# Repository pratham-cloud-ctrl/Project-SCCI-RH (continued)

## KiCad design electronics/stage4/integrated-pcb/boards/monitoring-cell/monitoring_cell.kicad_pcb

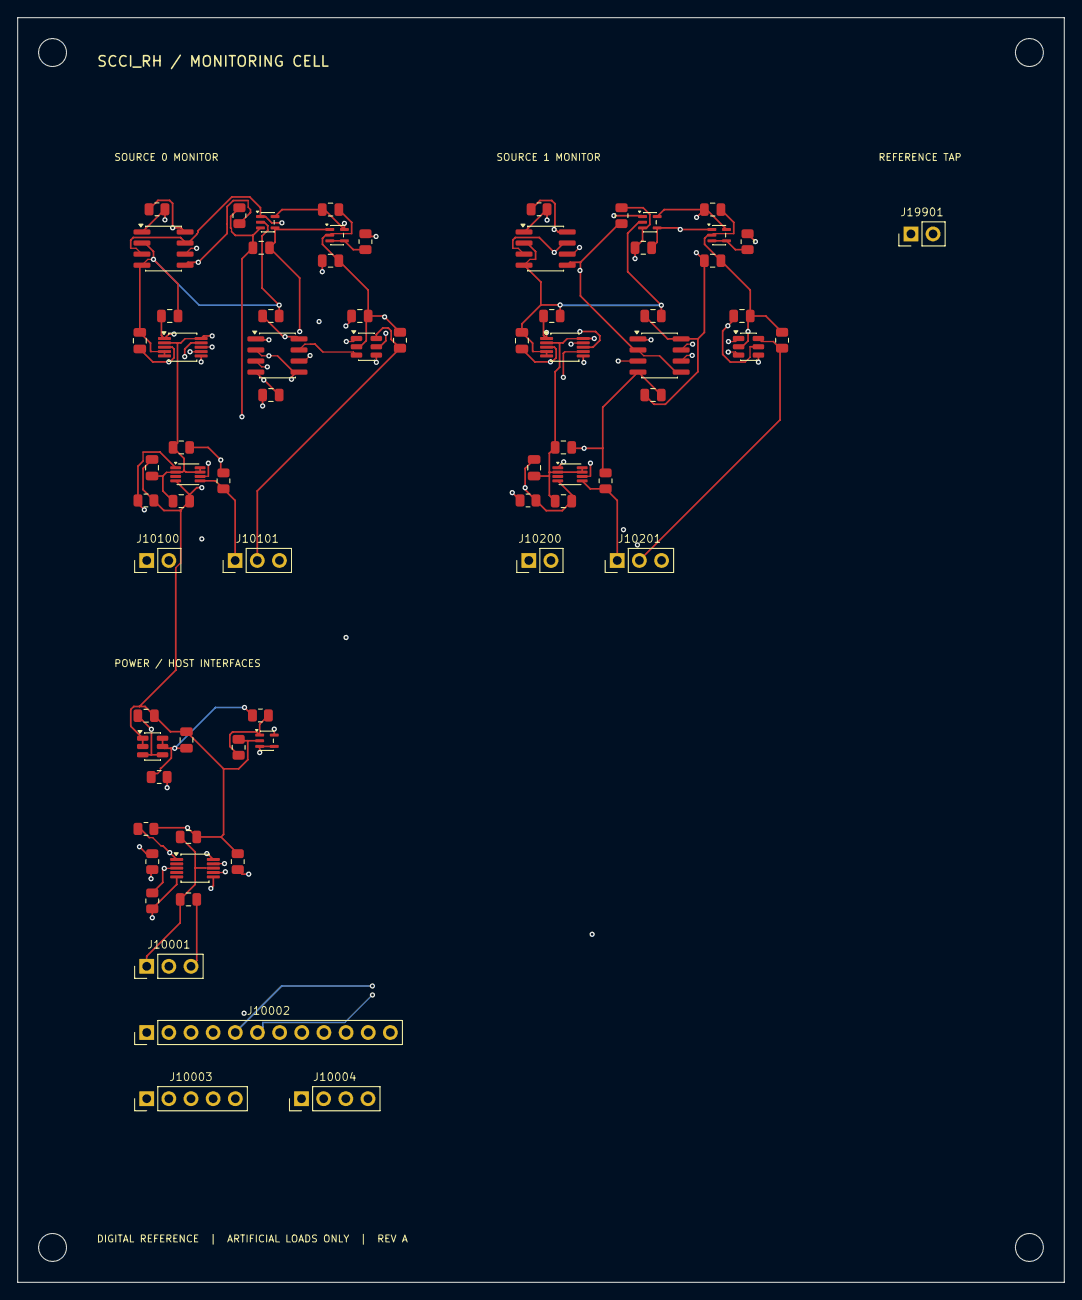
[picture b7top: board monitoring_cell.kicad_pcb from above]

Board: 4 copper layers, 120.0 x 145.0 mm, 75 parts (0 on the bottom side), 42 nets.

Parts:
C10001, C10002, C10105, C10106, C10205, C10206: 1u 10V; C_0805_2012Metric
C10003, C10004, C10102, C10103, C10104, C10108, C10109, C10110, C10202, C10203, C10204, C10208, C10209, C10210: 100n 10V; C_0805_2012Metric
C10100, C10200: 22n 0.5% C0G; C_0805_2012Metric
C10101, C10201: 1n C0G; C_0805_2012Metric
C10107, C10207: 22u 10V; C_0805_2012Metric
H1, H2, H3, H4: MountingHole_3.2mm_M3
J10001: LAB RAILS ONLY; PinHeader_1x03_P2.54mm_Vertical
J10002: MCU ENDPOINT/CONTROL; PinHeader_1x12_P2.54mm_Vertical
J10003: EXTERNAL SUPERVISION; PinHeader_1x05_P2.54mm_Vertical
J10004: CURRENT ADC INTERFACE; PinHeader_1x04_P2.54mm_Vertical
J10100: SOURCE 0 RETURN SHUNT; PinHeader_1x02_P2.54mm_Vertical
J10101: SOURCE 0 DRIVER PERMISSION; PinHeader_1x03_P2.54mm_Vertical
J10200: SOURCE 1 RETURN SHUNT; PinHeader_1x02_P2.54mm_Vertical
J10201: SOURCE 1 DRIVER PERMISSION; PinHeader_1x03_P2.54mm_Vertical
J19901: HOST TAP HARNESS; PinHeader_1x02_P2.54mm_Vertical
R10001, R10002, R10003, R10005, R10101, R10201: 10k 0.1%; R_0805_2012Metric
R10004: 19.1k 0.1%; R_0805_2012Metric
R10006, R10007, R10103, R10104, R10105, R10203, R10204, R10205: 100k; R_0805_2012Metric
R10100, R10200: 2R 0.1% KELVIN; R_0805_2012Metric
R10102, R10202: 33R; R_0805_2012Metric
U10001: REF3440DBVR; SOT-23-6
U10002, U10101, U10102, U10201, U10202: OPA391DCKR; SOT-353_SC-70-5
U10003: TMUX1136DGSR; MSOP-10_3x3mm_P0.5mm
U10100, U10200: INA241A2IDR; SOIC-8_3.9x4.9mm_P1.27mm
U10103, U10203: ADS8866IDGSR; MSOP-10_3x3mm_P0.5mm
U10104, U10204: TLV3202IDR; SOIC-8_3.9x4.9mm_P1.27mm
U10105, U10205: SN74LVC1G11DBVR; SOT-23-6
U10106, U10206: SN74LVC1G74DCUR; VSSOP-8_2.3x2mm_P0.5mm

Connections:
SYS_0d1e7c21__CH0_RETURN_LOAD: J10100.1, R10100.1, U10100.8
SYS_3ced048f__CH1_RETURN_LOAD: J10200.1, R10200.1, U10200.8
SYS_4f66f129__MON_VREF: C10002.1, C10107.1, C10207.1, J19901.1, R10001.1, R10003.1, U10001.5, U10001.6, U10103.1, U10203.1
SYS_7cf9dad5__MON_SCLK: J10002.7, U10103.8, U10203.8
SYS_32a601bf__MON_REARM1: J10002.11, R10204.1, U10206.1
SYS_36b0932b__INT_RUN1: J10002.9, R10007.1, U10003.5
SYS_37cfe02a__MON_VMID: J10004.3, U10002.3, U10002.4, U10100.3, U10100.7, U10101.1, U10200.3, U10200.7, U10201.1
SYS_56ebc071__CH0_MON_PERMIT: J10003.3, J10101.1, R10105.1, U10106.5
SYS_83a198be__CH0_DOUT: J10002.3, U10103.7
SYS_502efdd4__CH1_I_MON: J10004.2, R10201.1, U10200.5, U10204.2, U10204.5
SYS_822d2245__MON_REARM0: J10002.10, R10104.1, U10106.1
SYS_37737e7c__INT_RUN0: J10002.8, R10006.1, U10003.1
SYS_56562df4__GND: C10001.2, C10002.2, C10003.2, C10004.2, C10101.2, C10102.2, C10103.2, C10104.2, C10105.2, C10106.2, C10107.2, C10108.2, C10109.2, C10110.2, C10201.2, C10202.2, C10203.2, C10204.2, C10205.2, C10206.2, C10207.2, C10208.2, C10209.2, C10210.2, J10001.3, J10002.12, J10003.5, J10004.4, J10101.3, J10201.3, J19901.2, R10002.2, R10005.2, R10006.2, R10007.2, R10103.2, R10104.2, R10105.2, R10203.2, R10204.2, R10205.2, U10001.1, U10001.2, U10002.2, U10003.3, U10100.2, U10100.4, U10101.2, U10102.2, U10103.4, U10103.5, U10104.4, U10105.2, U10106.4, U10200.2, U10200.4, U10201.2, U10202.2, U10203.4, U10203.5, U10204.4, U10205.2, U10206.4
SYS_08572049__HOST_3V3: C10105.1, C10106.1, C10109.1, C10110.1, C10205.1, C10206.1, C10209.1, C10210.1, J10001.2, U10103.2, U10103.10, U10105.5, U10106.2, U10106.7, U10106.8, U10203.2, U10203.10, U10205.5, U10206.2, U10206.7, U10206.8
SYS_a863a08a__CS1: J10002.5, U10203.9
SYS_aa321af6__CH1_MON_PERMIT: J10003.4, J10201.1, R10205.1, U10206.5
SYS_c73180be__CH1_B_BR: J10200.2, R10200.2, U10200.1
SYS_ce0a4f53__BOTH_CNV: J10002.1, J10002.4, U10103.6, U10203.6
SYS_ce166826__HOST_5: C10001.1, C10003.1, C10004.1, C10102.1, C10103.1, C10104.1, C10108.1, C10202.1, C10203.1, C10204.1, C10208.1, J10001.1, U10001.3, U10001.4, U10002.5, U10003.8, U10100.6, U10101.5, U10102.5, U10104.8, U10200.6, U10201.5, U10202.5, U10204.8
SYS_d3eac10b__CH0_EXT_SUP_OK: J10003.1, J10101.2, R10103.1, U10105.6
SYS_de0a854a__CH1_EXT_SUP_OK: J10003.2, J10201.2, R10203.1, U10205.6
SYS_ec2c6e7f__CS0: J10002.2, U10103.9
SYS_ee476f53__CH0_B_BR: J10100.2, R10100.2, U10100.1
SYS_f8e43b73__CH0_I_MON: J10004.1, R10101.1, U10100.5, U10104.2, U10104.5
SYS_fd7db492__CH1_DOUT: J10002.6, U10203.7
monitoring-cell__CH0_ADC_BUF: R10102.1, U10102.3, U10102.4
monitoring-cell__CH0_ADC_IN: C10101.1, R10102.2, U10103.3
monitoring-cell__CH0_CLEAR_N: U10105.4, U10106.6
monitoring-cell__CH0_HI_OK: U10104.1, U10105.1
monitoring-cell__CH0_LO_OK: U10104.7, U10105.3
monitoring-cell__CH0_Q_INT: C10100.2, U10003.9, U10101.4, U10102.1
monitoring-cell__CH0_SUM: C10100.1, R10101.2, U10003.10, U10101.3
monitoring-cell__CH1_ADC_BUF: R10202.1, U10202.3, U10202.4
monitoring-cell__CH1_ADC_IN: C10201.1, R10202.2, U10203.3
monitoring-cell__CH1_CLEAR_N: U10205.4, U10206.6
monitoring-cell__CH1_HI_OK: U10204.1, U10205.1
monitoring-cell__CH1_LO_OK: U10204.7, U10205.3
monitoring-cell__CH1_Q_INT: C10200.2, U10003.7, U10201.4, U10202.1
monitoring-cell__CH1_SUM: C10200.1, R10201.2, U10003.6, U10201.3
monitoring-cell__I_HI: R10003.2, R10004.1, U10104.3, U10204.3
monitoring-cell__I_LO: R10004.2, R10005.1, U10104.6, U10204.6
monitoring-cell__MID_DIV: R10001.2, R10002.1, U10002.1

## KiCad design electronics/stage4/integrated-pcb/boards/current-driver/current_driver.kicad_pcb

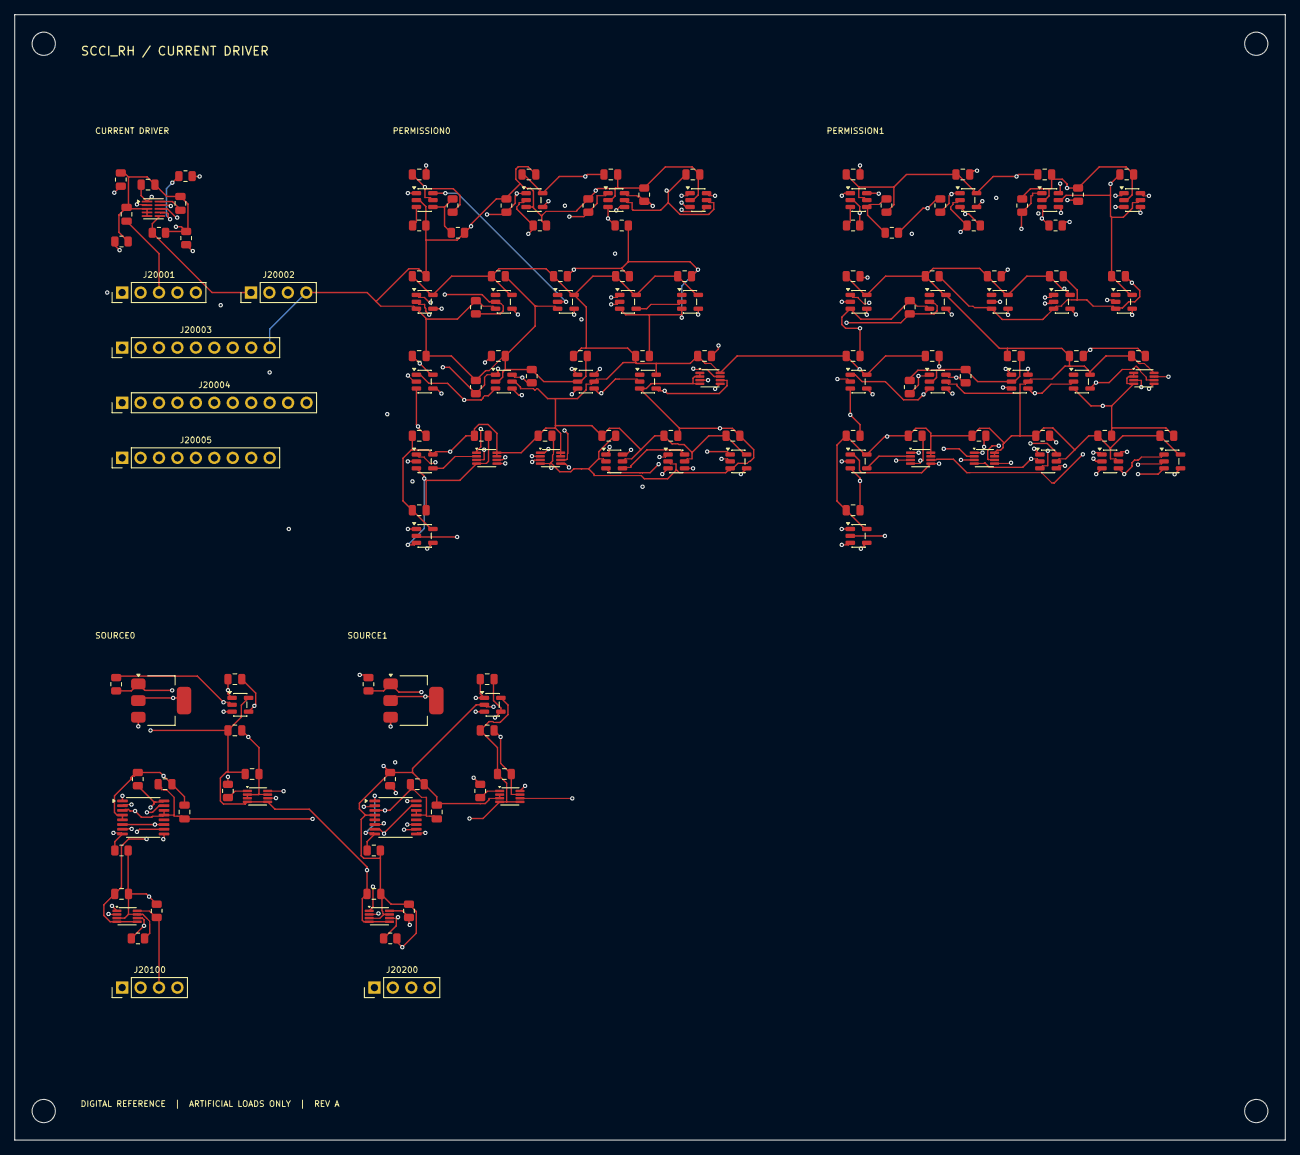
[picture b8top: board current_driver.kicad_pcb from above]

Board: 4 copper layers, 175.0 x 155.0 mm, 160 parts (0 on the bottom side), 96 nets.

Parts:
C20001, C20300, C20301, C20302, C20303, C20304, C20305, C20306, C20307, C20308, C20309, C20310, C20311, C20312, C20313, C20314, C20315, C20316, C20317, C20318, C20319, C20320, C20400, C20401, C20402, C20403, C20404, C20405, C20406, C20407, C20408, C20409, C20410, C20411, C20412, C20413, C20414, C20415, C20416, C20417, C20418, C20419, C20420: 100n 10V; C_0805_2012Metric
C20002: 4.7u 10V; C_0805_2012Metric
C20003: 220n 10V; C_0805_2012Metric
C20100, C20200: DNP 10p C0G; C_0805_2012Metric
C20101, C20102, C20103, C20201, C20202, C20203: 100n 25V; C_0805_2012Metric
C20104, C20204: 100n 50V; C_0805_2012Metric
C20105, C20205: 1u 50V; C_0805_2012Metric
H1, H2, H3, H4: MountingHole_3.2mm_M3
J20001: QUALIFIED EXTERNAL RAILS; PinHeader_1x05_P2.54mm_Vertical
J20002: MCU SPI / PRELOAD INHIBITED; PinHeader_1x04_P2.54mm_Vertical
J20003: MCU PHASE / EXPLICIT REARM; PinHeader_1x09_P2.54mm_Vertical
J20004: EXTERNAL HEALTH CONTRACTS; PinHeader_1x11_P2.54mm_Vertical
J20005: STATUS ONLY / NOT DELIVERY EVIDENCE; PinHeader_1x09_P2.54mm_Vertical
J20100, J20200: EXTERNAL ROUTER / MONITOR; PinHeader_1x04_P2.54mm_Vertical
Q20100, Q20200: BSP89H6327XTSA1; BSP89_PG-SOT223-4_DrainTab
R20001, R20002, R20003, R20004, R20005, R20303, R20304, R20305, R20306, R20307, R20308, R20309, R20310, R20403, R20404, R20405, R20406, R20407, R20408, R20409, R20410: 10k; R_0805_2012Metric
R20100, R20200: 100R 0.1% LOW TCR; R_0805_2012Metric
R20101, R20201: 330R; R_0805_2012Metric
R20102, R20202: 100k; R_0805_2012Metric
R20103, R20104, R20105, R20203, R20204, R20205: 22k; R_0805_2012Metric
R20300, R20400: 175.8k 0.1%; R_0805_2012Metric
R20301, R20401: 976k 0.1%; R_0805_2012Metric
R20302, R20402: 182k 0.1%; R_0805_2012Metric
U20001: DAC80502DRXR; Texas_DRX_WSON-10_2.5x2.5mm_P0.5mm
U20100, U20200: OPA192IDBVR; SOT-23-5
U20101, U20201: TMUX7212PWR; TSSOP-16_4.4x5mm_P0.65mm
U20102, U20103, U20202, U20203: TMUX6219DGKR; VSSOP-8_2.3x2mm_P0.5mm
U20300, U20400: LTC6993HS6-1#TRPBF; TSOT-23-6
U20301, U20401: SN74LVC1G86DBVR; SOT-23-5
U20302, U20303, U20310, U20311, U20317, U20318, U20402, U20403, U20410, U20411, U20417, U20418: SN74LVC1G11DBVR; SOT-23-6
U20304, U20307, U20309, U20319, U20320, U20404, U20407, U20409, U20419, U20420: SN74LVC1G08DBVR; SOT-23-5
U20305, U20306, U20308, U20312, U20405, U20406, U20408, U20412: SN74LVC1G04DBVR; SOT-23-5
U20313, U20315, U20316, U20413, U20415, U20416: SN74LVC1G74DCUR; VSSOP-8_2.3x2mm_P0.5mm
U20314, U20414: SN74LVC1G32DBVR; SOT-23-5

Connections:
SYS_2d0e5b2e__CH0_QUIESCENT_OK: J20004.6, R20310.1, U20310.6
SYS_3abe1caf__BOTH_DRV_REARM: J20003.4, J20003.8, R20306.1, R20406.1, U20310.1, U20410.1
SYS_3b27d056__MINUS0: J20003.3, R20305.1, U20301.2
SYS_6a132103__CH1_RUN: J20005.5, R20205.1, U20202.6, U20203.6, U20418.4, U20419.1, U20420.1
SYS_9c8a42b1__CH1_TIMEOUT: J20005.7, U20414.1, U20415.5
SYS_11f4403a__ROUTE_SER: J20002.3, R20002.1, U20001.8
SYS_20eba8c2__CH1_QUIESCENT_OK: J20004.10, R20410.1, U20410.6
SYS_46ea5f03__CH0_REQUEST: J20003.1, R20303.1, U20300.1, U20305.2, U20314.2, U20318.1
SYS_54dd20d7__CH0_TIMEOUT: J20005.3, U20314.1, U20315.5
SYS_56ebc071__CH0_MON_PERMIT: J20004.3, R20307.1, U20302.1
SYS_84f28705__CH1_ROUTE_LOCKED: J20004.9, R20409.1, U20402.6
SYS_401be33b__CH1_A_ROUTER: J20200.1, U20201.2, U20201.10
SYS_628d7747__PLUS1: J20003.6, R20404.1, U20401.1, U20416.2
SYS_695f3a7c__CH0_RUN: J20005.1, R20105.1, U20102.6, U20103.6, U20318.4, U20319.1, U20320.1
SYS_917b1360__CH0_A_ROUTER: J20100.1, U20101.2, U20101.10
SYS_973f460c__PLUS0: J20003.2, R20304.1, U20301.1, U20316.2
SYS_8359fceb__CH1_EXT_SUP_OK: J20004.8, R20408.1, U20402.3
SYS_15689dc4__VH_24: C20104.1, C20105.1, C20204.1, C20205.1, J20001.1, U20101.3, U20101.13, U20101.14, U20201.3, U20201.13, U20201.14
SYS_56562df4__GND: C20001.2, C20002.2, C20003.2, C20101.2, C20102.2, C20103.2, C20104.2, C20105.2, C20201.2, C20202.2, C20203.2, C20204.2, C20205.2, C20300.2, C20301.2, C20302.2, C20303.2, C20304.2, C20305.2, C20306.2, C20307.2, C20308.2, C20309.2, C20310.2, C20311.2, C20312.2, C20313.2, C20314.2, C20315.2, C20316.2, C20317.2, C20318.2, C20319.2, C20320.2, C20400.2, C20401.2, C20402.2, C20403.2, C20404.2, C20405.2, C20406.2, C20407.2, C20408.2, C20409.2, C20410.2, C20411.2, C20412.2, C20413.2, C20414.2, C20415.2, C20416.2, C20417.2, C20418.2, C20419.2, C20420.2, J20001.5, J20002.4, J20003.9, J20004.11, J20005.9, J20100.4, J20200.4, R20001.2, R20002.2, R20004.2, R20005.2, R20100.2, R20102.2, R20103.2, R20104.2, R20105.2, R20200.2, R20202.2, R20203.2, R20204.2, R20205.2, R20300.2, R20302.2, R20303.2, R20304.2, R20305.2, R20306.2, R20307.2, R20308.2, R20309.2, R20310.2, R20400.2, R20402.2, R20403.2, R20404.2, R20405.2, R20406.2, R20407.2, R20408.2, R20409.2, R20410.2, U20001.3, U20001.4, U20001.5, U20100.2, U20101.4, U20101.5, U20102.2, U20102.3, U20102.7, U20103.3, U20103.7, U20200.2, U20201.4, U20201.5, U20202.2, U20202.3, U20202.7, U20203.3, U20203.7, U20300.2, U20301.3, U20302.2, U20303.2, U20304.3, U20305.3, U20306.3, U20307.3, U20308.3, U20309.3, U20310.2, U20311.2, U20312.3, U20313.1, U20313.2, U20313.4, U20314.3, U20315.4, U20316.4, U20317.2, U20318.2, U20319.3, U20320.3, U20400.2, U20401.3, U20402.2, U20403.2, U20404.3, U20405.3, U20406.3, U20407.3, U20408.3, U20409.3, U20410.2, U20411.2, U20412.3, U20413.1, U20413.2, U20413.4, U20414.3, U20415.4, U20416.4, U20417.2, U20418.2, U20419.3, U20420.3
SYS_1954027d__CH0_ROUTE_LOCKED: J20004.5, R20309.1, U20302.6
SYS_08572049__HOST_3V3: C20300.1, C20301.1, C20302.1, C20303.1, C20304.1, C20305.1, C20306.1, C20307.1, C20308.1, C20309.1, C20310.1, C20311.1, C20312.1, C20313.1, C20314.1, C20315.1, C20316.1, C20317.1, C20318.1, C20319.1, C20320.1, C20400.1, C20401.1, C20402.1, C20403.1, C20404.1, C20405.1, C20406.1, C20407.1, C20408.1, C20409.1, C20410.1, C20411.1, C20412.1, C20413.1, C20414.1, C20415.1, C20416.1, C20417.1, C20418.1, C20419.1, C20420.1, J20001.4, R20003.2, R20301.1, R20401.1, U20300.5, U20301.5, U20302.5, U20303.5, U20304.5, U20305.5, U20306.5, U20307.5, U20308.5, U20309.5, U20310.5, U20311.5, U20312.5, U20313.8, U20314.5, U20315.7, U20315.8, U20316.7, U20316.8, U20317.5, U20318.5, U20319.5, U20320.5, U20400.5, U20401.5, U20402.5, U20403.5, U20404.5, U20405.5, U20406.5, U20407.5, U20408.5, U20409.5, U20410.5, U20411.5, U20412.5, U20413.8, U20414.5, U20415.7, U20415.8, U20416.7, U20416.8, U20417.5, U20418.5, U20419.5, U20420.5
SYS_93547907__RAILS_QUALIFIED: J20004.2, R20005.1, U20303.3, U20403.3
SYS_aa321af6__CH1_MON_PERMIT: J20004.7, R20407.1, U20402.1
SYS_c659d53f__CH1_TIMER: J20005.8, U20400.6, U20406.2, U20407.1, U20418.3
SYS_c73180be__CH1_B_BR: J20200.2, U20201.7, U20201.15
SYS_ca7ea3db__CH0_TIMER: J20005.4, U20300.6, U20306.2, U20307.1, U20318.3
SYS_ce166826__HOST_5: C20001.1, C20002.1, J20001.3, U20001.1
SYS_d5e1f64a__ROUTE_SRCLK: J20002.1, R20001.1, U20001.6
SYS_dd388269__CH1_REQUEST: J20003.5, R20403.1, U20400.1, U20405.2, U20414.2, U20418.1
SYS_e496c0b2__DAC_SYNC_N: J20002.2, R20003.1, U20001.7
SYS_e26747fb__CH0_EXT_SUP_OK: J20004.4, R20308.1, U20302.3
SYS_edc800df__MINUS1: J20003.7, R20405.1, U20401.2
SYS_ee476f53__CH0_B_BR: J20100.2, U20101.7, U20101.15
SYS_fb2237f8__VA_15: C20101.1, C20102.1, C20103.1, C20201.1, C20202.1, C20203.1, J20001.2, U20100.5, U20102.4, U20102.5, U20103.4, U20103.5, U20200.5, U20202.4, U20202.5, U20203.4, U20203.5
SYS_ff7fdc58__RESET_READY: J20004.1, R20004.1, U20303.1, U20316.6, U20403.1, U20416.6
current-driver__CH0_BASE_GOOD: U20304.4, U20309.1, U20310.3, U20317.1
current-driver__CH0_BLOCK: J20005.2, U20313.5
current-driver__CH0_BLOCK_N: U20313.3, U20317.3
current-driver__CH0_BLOCK_PRE_N: U20309.4, U20313.7
current-driver__CH0_DIAG_M: R20104.1, U20101.9, U20101.16, U20320.4
current-driver__CH0_DIAG_P: R20103.1, U20101.1, U20101.8, U20319.4
current-driver__CH0_FB: C20100.2, U20100.4, U20103.1
current-driver__CH0_GATE: Q20100.1, R20101.2, R20102.1
current-driver__CH0_GATE_SW: R20101.1, U20102.1
current-driver__CH0_GOOD: U20317.4, U20318.6
current-driver__CH0_HEALTH_A: U20302.4, U20304.1
current-driver__CH0_HEALTH_B: U20303.4, U20304.2
current-driver__CH0_LATCH_CLR_N: U20312.4, U20313.6, U20315.6
current-driver__CH0_MINUS_LATCHED: U20316.3, U20320.2
current-driver__CH0_PLUS_LATCHED: U20316.5, U20319.2
current-driver__CH0_REARM_A: U20310.4, U20311.1
current-driver__CH0_REQ_N: U20305.4, U20307.2, U20311.3
current-driver__CH0_SAFE_REARM: U20311.4, U20312.2, U20316.1
current-driver__CH0_SENSE_K: J20100.3, Q20100.3, R20100.1, U20103.8
current-driver__CH0_SERVO: C20100.1, U20100.1, U20102.8, U20103.2
current-driver__CH0_SINK_D: Q20100.2, Q20100.4, U20101.6, U20101.11
current-driver__CH0_STOP_CONSUME: U20307.4, U20308.2
current-driver__CH0_STOP_N: U20308.4, U20309.2
current-driver__CH0_TIMEOUT_D: U20314.4, U20315.2
current-driver__CH0_TIMEOUT_N: U20315.3, U20317.6
current-driver__CH0_TIMER_N: U20306.4, U20311.6, U20315.1
current-driver__CH0_T_DIV: R20301.2, R20302.1, U20300.4
current-driver__CH0_T_SET: R20300.1, U20300.3
current-driver__CH0_VALID_DIR: U20301.4, U20303.6
current-driver__CH0_VSET: U20001.2, U20100.3
current-driver__CH1_BASE_GOOD: U20404.4, U20409.1, U20410.3, U20417.1
current-driver__CH1_BLOCK: J20005.6, U20413.5
current-driver__CH1_BLOCK_N: U20413.3, U20417.3
current-driver__CH1_BLOCK_PRE_N: U20409.4, U20413.7
current-driver__CH1_DIAG_M: R20204.1, U20201.9, U20201.16, U20420.4
current-driver__CH1_DIAG_P: R20203.1, U20201.1, U20201.8, U20419.4
current-driver__CH1_FB: C20200.2, U20200.4, U20203.1
current-driver__CH1_GATE: Q20200.1, R20201.2, R20202.1
current-driver__CH1_GATE_SW: R20201.1, U20202.1
current-driver__CH1_GOOD: U20417.4, U20418.6
current-driver__CH1_HEALTH_A: U20402.4, U20404.1
current-driver__CH1_HEALTH_B: U20403.4, U20404.2
current-driver__CH1_LATCH_CLR_N: U20412.4, U20413.6, U20415.6
current-driver__CH1_MINUS_LATCHED: U20416.3, U20420.2
current-driver__CH1_PLUS_LATCHED: U20416.5, U20419.2
current-driver__CH1_REARM_A: U20410.4, U20411.1
current-driver__CH1_REQ_N: U20405.4, U20407.2, U20411.3
current-driver__CH1_SAFE_REARM: U20411.4, U20412.2, U20416.1
current-driver__CH1_SENSE_K: J20200.3, Q20200.3, R20200.1, U20203.8
current-driver__CH1_SERVO: C20200.1, U20200.1, U20202.8, U20203.2
current-driver__CH1_SINK_D: Q20200.2, Q20200.4, U20201.6, U20201.11
current-driver__CH1_STOP_CONSUME: U20407.4, U20408.2
current-driver__CH1_STOP_N: U20408.4, U20409.2
current-driver__CH1_TIMEOUT_D: U20414.4, U20415.2
current-driver__CH1_TIMEOUT_N: U20415.3, U20417.6
current-driver__CH1_TIMER_N: U20406.4, U20411.6, U20415.1
current-driver__CH1_T_DIV: R20401.2, R20402.1, U20400.4
current-driver__CH1_T_SET: R20400.1, U20400.3
current-driver__CH1_VALID_DIR: U20401.4, U20403.6
current-driver__CH1_VSET: U20001.9, U20200.3
current-driver__DAC_VREF: C20003.1, U20001.10

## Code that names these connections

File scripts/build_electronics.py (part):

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def r(ref,value,a,b,xy,group,desc): add(ref,value,RFP,{1:a,2:b},xy,group,desc,"0805 thin-film, 0.1%, >=0.125 W")
def c(ref,value,a,b,xy,group,desc): add(ref,value,CFP,{1:a,2:b},xy,group,desc,"0805 ceramic, X7R, >=10 V, 10%")
add("J1","5V INPUT","Connector_PinHeader_2.54mm:PinHeader_1x02_P2.54mm_Vertical",{1:"+5V",2:"GND"},(5,24),"power","External regulated 5 V only; no isolation or regulator")
add("J2","ARTIFICIAL IN","Connector_PinHeader_2.54mm:PinHeader_1x03_P2.54mm_Vertical",{1:"SIG_IN",2:"GND",3:"MID"},(3,13),"recording","Function-generator input and midpoint monitor")
add("J3","ANALOG OUT","Connector_PinHeader_2.54mm:PinHeader_1x03_P2.54mm_Vertical",{1:"REC_OUT",2:"GND",3:"MID"},(3,32),"recording","High-impedance external ADC/scope, not populated")
add("U1","OPA2333AID",SO8,{1:"REC_AMP",2:"REC_FB",3:"REC_IN",4:"GND",5:"MID_RAW",6:"MID",7:"MID",8:"+5V"},(25,20),"recording","A: AC-coupled gain 21; B: midpoint follower","OPA2333AID")
r("R1","10k","SIG_IN","AC_IN",(16,13),"recording","Input series impedance; not patient protection")
c("C1","1u","AC_IN","REC_IN",(20,13),"recording","Input AC coupling, 0.158 Hz corner with R1+R2")
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c("C7","100n","+5V","GND",(55,10),"power","U3 local supply bypass")
r("R14","12k","SW_A","DUT_A",(68,27),"stimulation","Revision B series output resistance, leg A")
r("R15","12k","SW_B","DUT_B",(66,34),"stimulation","Revision B series output resistance, leg B")
add("J4","5V LOGIC","Connector_PinHeader_2.54mm:PinHeader_1x04_P2.54mm_Vertical",{1:"PHASE",2:"INHIBIT",3:"+5V",4:"GND"},(74,16),"control","External phase/inhibit sequencer; 5 V CMOS logic required")
add("J5","DUMMY LOAD","Connector_PinHeader_2.54mm:PinHeader_1x02_P2.54mm_Vertical",{1:"DUT_A",2:"DUT_B"},(74,32),"stimulation","External electrical test load only")

# Local footprint snapshots make source editable without absolute library paths.
fpdir=OUT/"scci_rh.pretty"; fpdir.mkdir(exist_ok=True)
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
